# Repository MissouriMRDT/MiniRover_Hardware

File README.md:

# Mini Rover 
A board to control the drivetrain, arm, and LED panel of a miniature rover. The miniature rover can be controlled via a web interface on the user’s phone served over a wifi access point by the mini rover. 

[Main Project Document](https://mailmissouri.sharepoint.com/:w:/r/sites/SDELC-MarsRoverDesignTeam-Ogrp/_layouts/15/Doc.aspx?sourcedoc=%7B7972E1ED-EA8C-4D12-BFD3-157AE2B669ED%7D&file=Mini%20Rover.docx&action=default&mobileredirect=true)

[Discord Forum](https://discord.com/channels/988649090306961418/1412217151716196412)

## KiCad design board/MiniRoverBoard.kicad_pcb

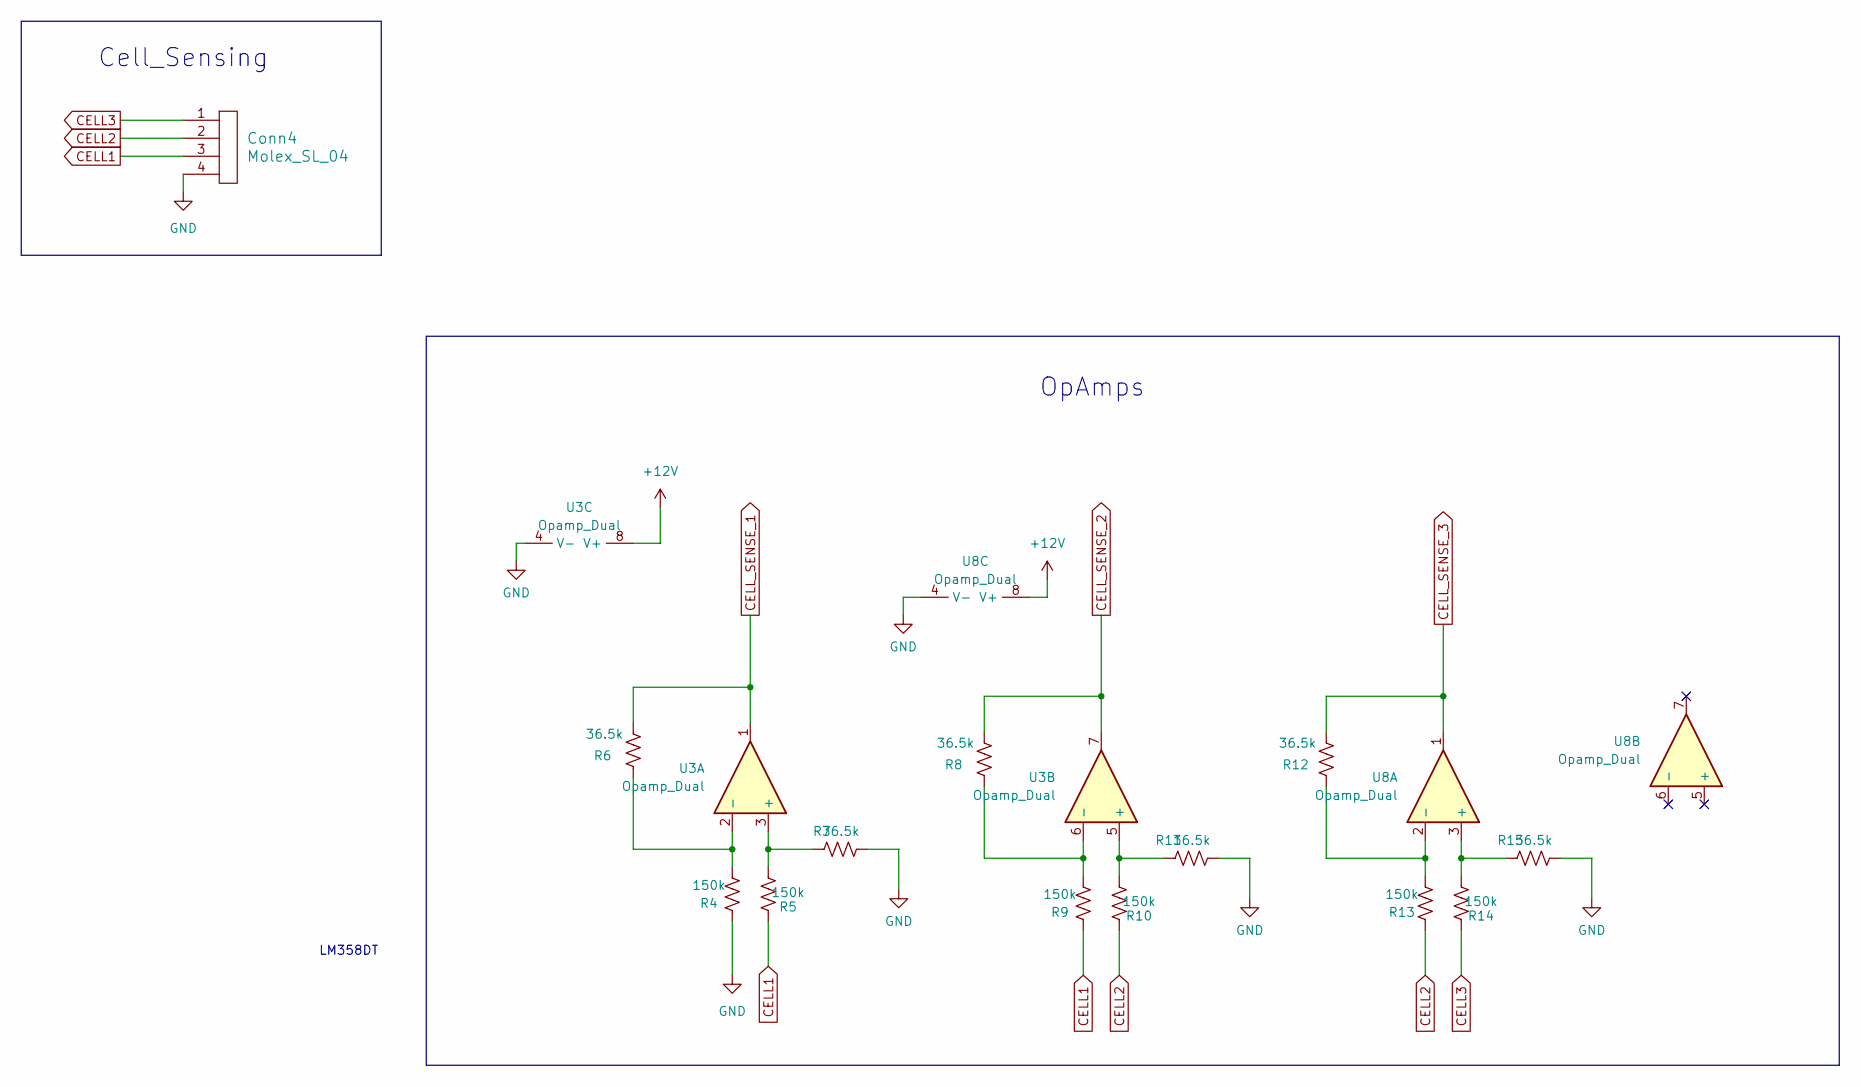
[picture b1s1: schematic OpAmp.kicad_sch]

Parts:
Conn4: Molex_SL_04; MOLEX_SL_04_Vertical
R4, R5, R9, R10, R13, R14: 150k; R_0603_1608Metric_Pad0.98x0.95mm_HandSolder
R6, R7, R8, R11, R12, R15: 36.5k; R_0603_1608Metric_Pad0.98x0.95mm_HandSolder
U3, U8: Opamp_Dual; SO-8_3.9x4.9mm_P1.27mm

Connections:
+12V: U3.8 (V+), U8.8 (V+); also elsewhere on the board
CELL1: Conn4.3, R5.1, R9.1
CELL2: Conn4.2, R10.1, R13.1
CELL3: Conn4.1, R14.1
CELL_SENSE_1: R6.2, U3.1; also elsewhere on the board
CELL_SENSE_2: R8.2, U3.7; also elsewhere on the board
CELL_SENSE_3: R12.2, U8.1; also elsewhere on the board
GND: Conn4.4, R4.1, R7.2, R11.2, R15.2, U3.4 (V-), U8.4 (V-); also elsewhere on the board
unnamed: R5.2, R7.1, U3.3 (+)
unnamed: R4.2, R6.1, U3.2 (-)
unnamed: R10.2, R11.1, U3.5 (+)
unnamed: R8.1, R9.2, U3.6 (-)
unnamed: R14.2, R15.1, U8.3 (+)
unnamed: R12.1, R13.2, U8.2 (-)

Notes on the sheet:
OpAmps
LM358DT
Cell_Sensing

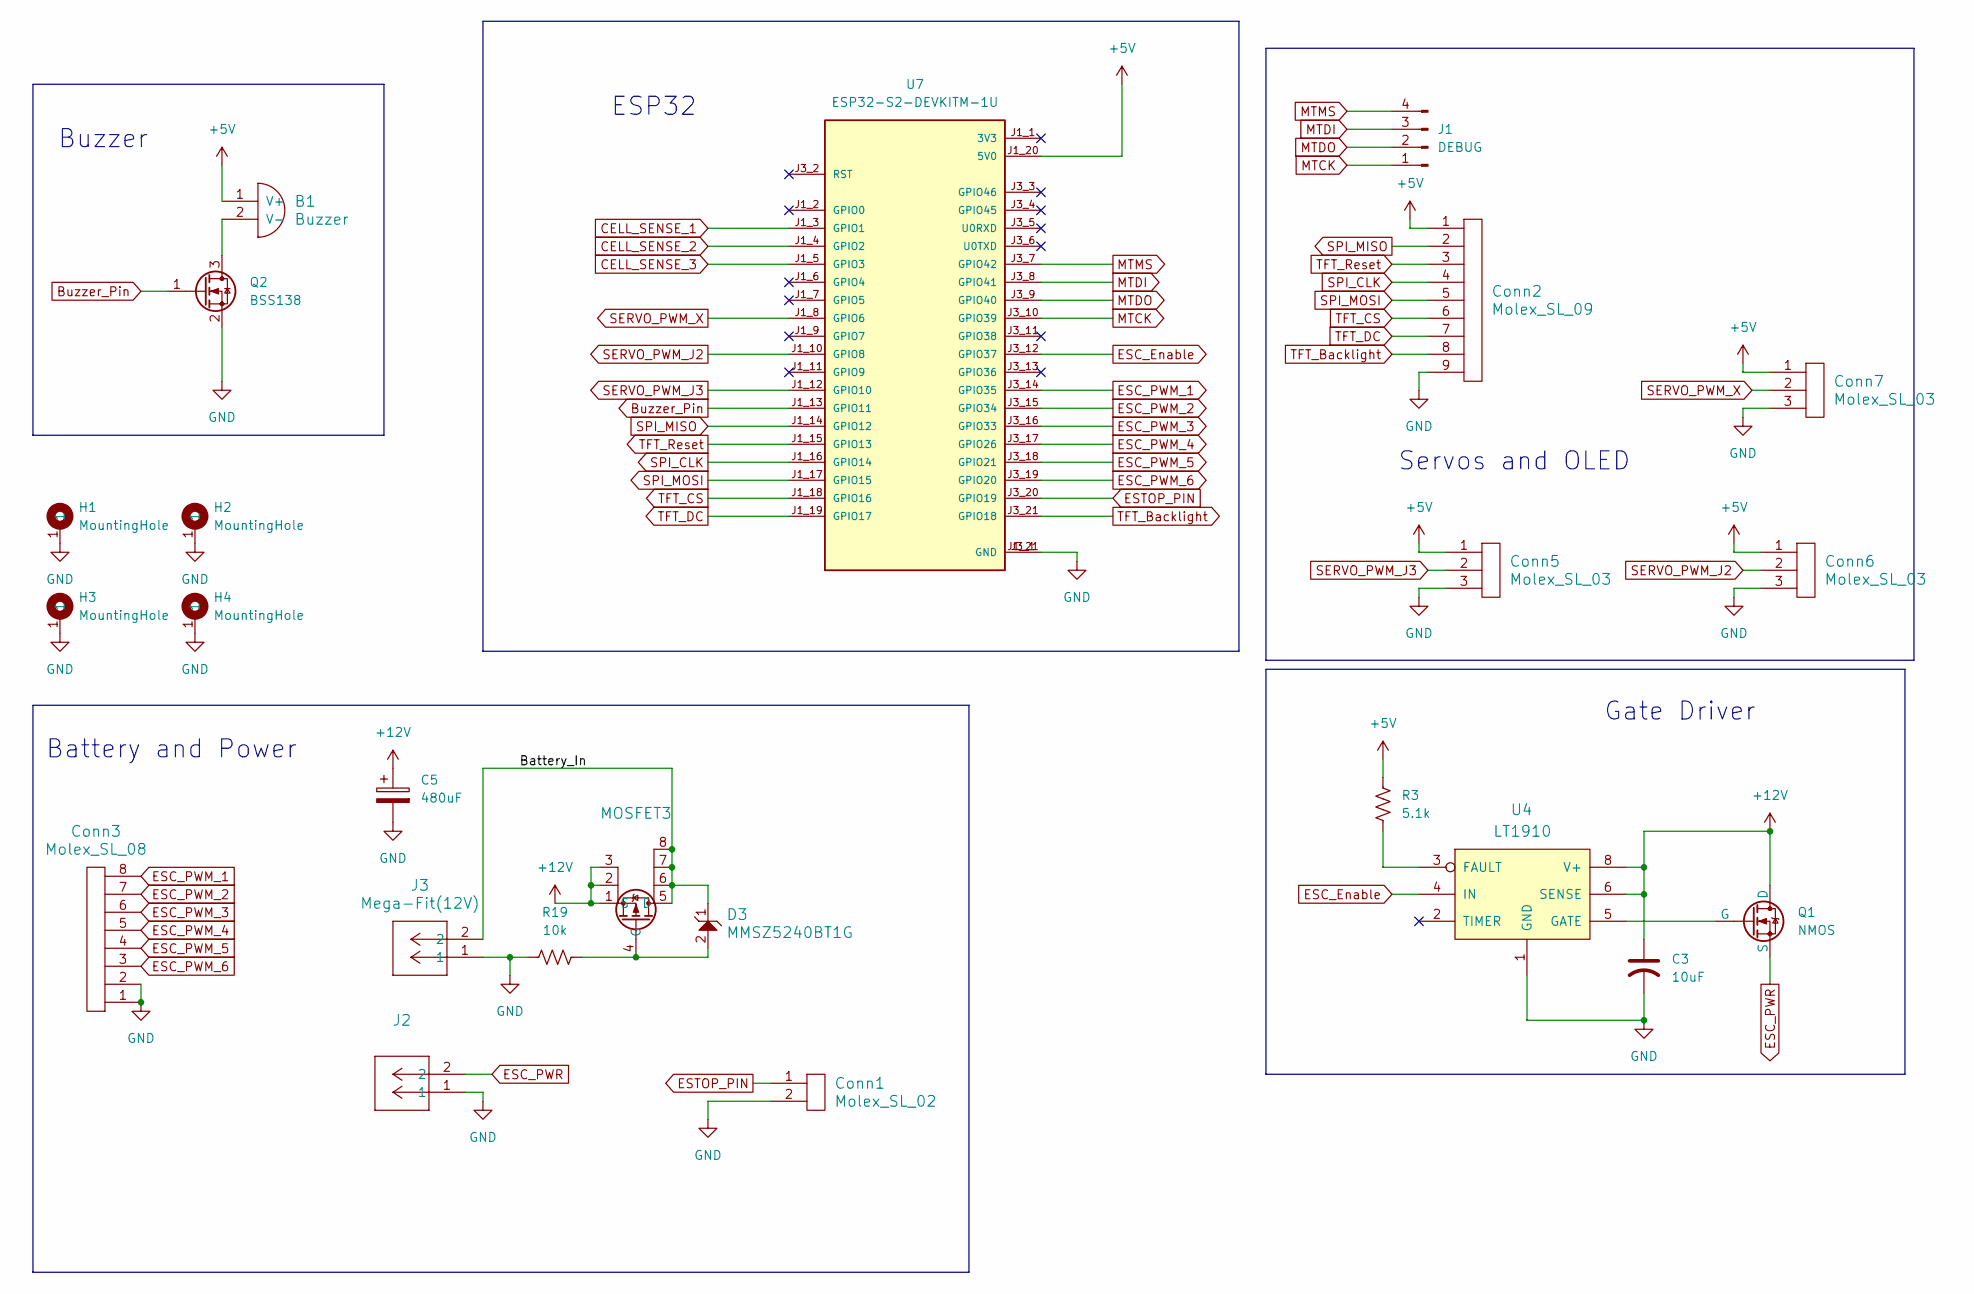
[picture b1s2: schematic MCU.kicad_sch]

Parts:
B1: Buzzer; Buzzer_12x9.5RM7.6
C3: 10uF; C_0603_1608Metric_Pad1.08x0.95mm_HandSolder
C5: 480uF; CP_Radial_D10.0mm_P5.00mm
Conn1: Molex_SL_02; MOLEX_SL_02_Vertical
Conn2: Molex_SL_09; MOLEX_SL_09_Vertical
Conn3: Molex_SL_08; MOLEX_SL_08_Vertical
Conn5, Conn6, Conn7: Molex_SL_03; MOLEX_SL_03_Vertical
D3: MMSZ5240BT1G; SOD-123_ONS-L
H1, H2, H3, H4: MountingHole; 4_40_Hole_Pad_Via
J1: DEBUG; PinSocket_1x04_P2.54mm_Vertical
J2: Mega-Fit(ESC_PWR); MOLEX_MegaFit_02_Horizontal
J3: Mega-Fit(12V); MOLEX_MegaFit_02_Horizontal
MOSFET3: TPC8132_LQS; SOP-8_TOS-L
Q1: NMOS; TO-252-3_TabPin2
Q2: BSS138; SOT-23
R3: 5.1k; R_0603_1608Metric_Pad0.98x0.95mm_HandSolder
R19: 10k; R_0603_1608Metric_Pad0.98x0.95mm_HandSolder
U4: LT1910; SOIC-8_3.9x4.9mm_P1.27mm
U7: ESP32-S2-DEVKITM-1U; XCVR_ESP32-S2-DEVKITM-1U; PARTREV 1.0

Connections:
+5V: B1.1 (V+), Conn2.1, Conn5.1, Conn6.1, Conn7.1, R3.1, U7.J1_20 (5V0); also elsewhere on the board
+12V: C3.1, C5.1, MOSFET3.1 (S), MOSFET3.2, MOSFET3.3, Q1.2 (D), U4.6 (SENSE), U4.8 (V+); also elsewhere on the board
/MCU/Battery_In: D3.1, J3.2, MOSFET3.5 (D), MOSFET3.6, MOSFET3.7, MOSFET3.8
Buzzer_Pin: Q2.1 (G), U7.J1_13 (GPIO11)
CELL_SENSE_1: U7.J1_3 (GPIO1); also elsewhere on the board
CELL_SENSE_2: U7.J1_4 (GPIO2); also elsewhere on the board
CELL_SENSE_3: U7.J1_5 (GPIO3); also elsewhere on the board
ESC_Enable: U4.4 (IN), U7.J3_12 (GPIO37)
ESC_PWM_1: Conn3.8, U7.J3_14 (GPIO35)
ESC_PWM_2: Conn3.7, U7.J3_15 (GPIO34)
ESC_PWM_3: Conn3.6, U7.J3_16 (GPIO33)
ESC_PWM_4: Conn3.5, U7.J3_17 (GPIO26)
ESC_PWM_5: Conn3.4, U7.J3_18 (GPIO21)
ESC_PWM_6: Conn3.3, U7.J3_19 (GPIO20)
ESC_PWR: J2.2, Q1.3 (S)
ESTOP_PIN: Conn1.1, U7.J3_20 (GPIO19)
GND: C3.2, C5.2, Conn1.2, Conn2.9, Conn3.1, Conn3.2, Conn5.3, Conn6.3, Conn7.3, H1.1, H2.1, H3.1, H4.1, J2.1, J3.1, Q2.2 (S), R19.1, U4.1 (GND), U7.J1_21 (GND), U7.J3_1 (GND); also elsewhere on the board
MTCK: J1.1, U7.J3_10 (GPIO39)
MTDI: J1.3, U7.J3_8 (GPIO41)
MTDO: J1.2, U7.J3_9 (GPIO40)
MTMS: J1.4, U7.J3_7 (GPIO42)
unnamed: B1.2 (V-), Q2.3 (D)
unnamed: D3.2, MOSFET3.4 (G), R19.2
unnamed: Q1.1 (G), U4.5 (GATE)
unnamed: R3.2, U4.3 (FAULT)
SERVO_PWM_J2: Conn6.2, U7.J1_10 (GPIO8)
SERVO_PWM_J3: Conn5.2, U7.J1_12 (GPIO10)
SERVO_PWM_X: Conn7.2, U7.J1_8 (GPIO6)
SPI_CLK: Conn2.4, U7.J1_16 (GPIO14)
SPI_MISO: Conn2.2, U7.J1_14 (GPIO12)
SPI_MOSI: Conn2.5, U7.J1_17 (GPIO15)
TFT_Backlight: Conn2.8, U7.J3_21 (GPIO18)
TFT_CS: Conn2.6, U7.J1_18 (GPIO16)
TFT_DC: Conn2.7, U7.J1_19 (GPIO17)
TFT_Reset: Conn2.3, U7.J1_15 (GPIO13)

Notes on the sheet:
Buzzer
Servos and OLED
Gate Driver
ESP32
Battery and Power

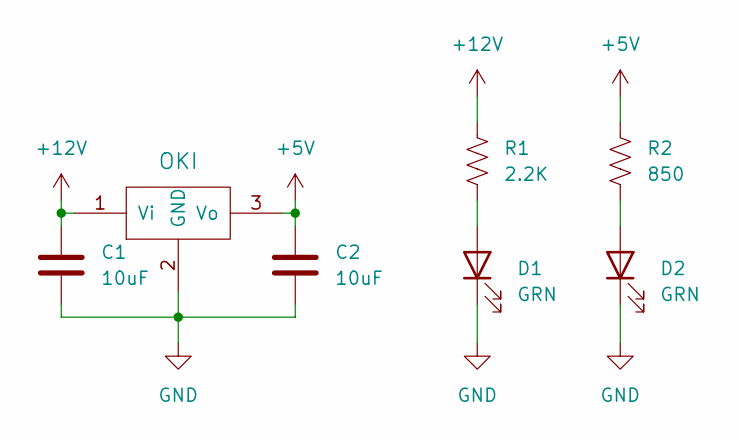
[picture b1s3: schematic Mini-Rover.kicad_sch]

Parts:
C1, C2: 10uF; C_0603_1608Metric_Pad1.08x0.95mm_HandSolder
D1, D2: GRN; LED_0603_1608Metric_Pad1.05x0.95mm_HandSolder
R1: 2.2K; R_0603_1608Metric_Pad0.98x0.95mm_HandSolder
R2: 850; R_0603_1608Metric_Pad0.98x0.95mm_HandSolder
U2: OKI; OKI_Horizontal

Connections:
+5V: C2.1, R2.1, U2.3 (Vo); also elsewhere on the board
+12V: C1.2, R1.1, U2.1 (Vi); also elsewhere on the board
GND: C1.1, C2.2, D1.1 (K), D2.1 (K), U2.2 (GND); also elsewhere on the board
unnamed: D1.2 (A), R1.2
unnamed: D2.2 (A), R2.2

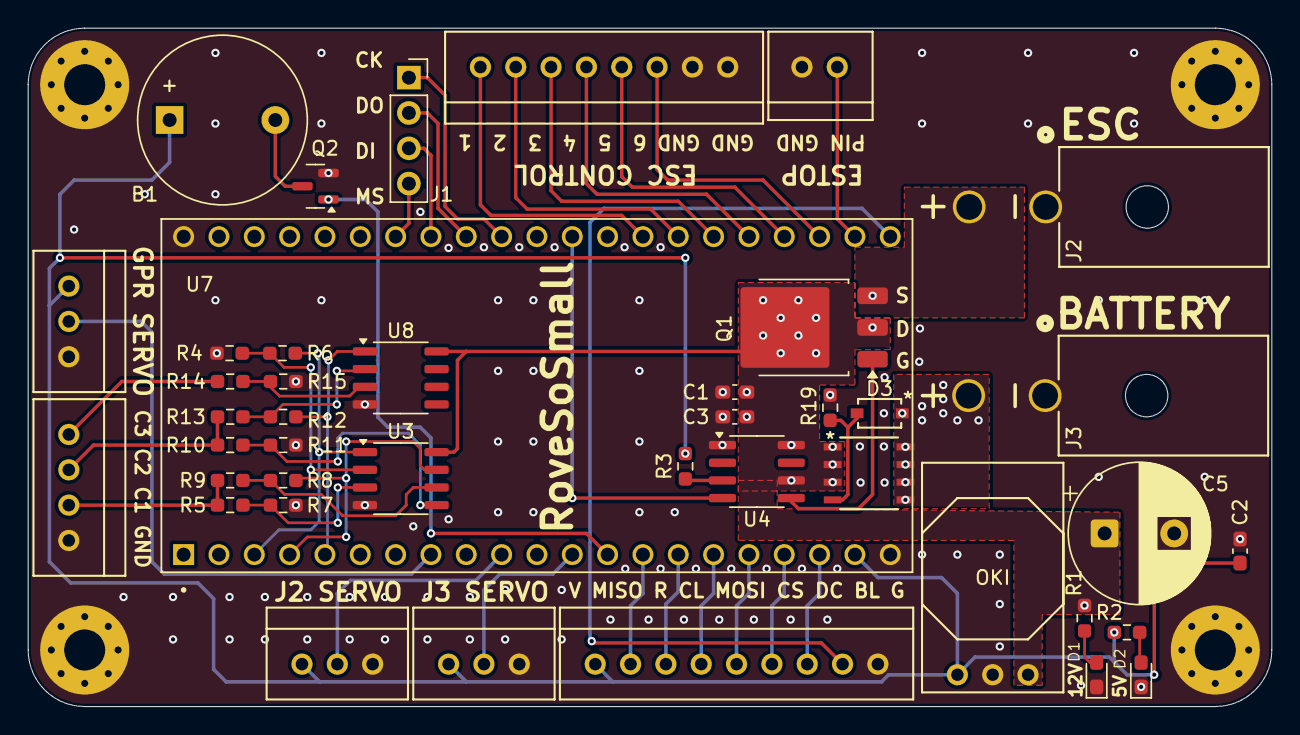
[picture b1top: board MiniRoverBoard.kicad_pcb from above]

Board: 2 copper layers, 89.4 x 48.8 mm, 46 parts (0 on the bottom side), 46 nets.

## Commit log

2025-09-12 Add workflows
2025-09-12 Added workflow
2025-10-02 Oki 12v -> 5v
2025-10-07 small fixes + 3.3V line
2025-10-07 Estop circuit
2025-10-08 Add cell sensing opamp
2025-10-08 connecting pins
2025-10-08 connections
2025-10-08 Need different mosfet/gate driver
2025-10-13 Add Gate Driver
2025-10-15 Add Gate Driver Circuit
2025-10-15 Add Gate Driver Resistor & Capacitor Values
2025-10-22 Add Gate_IN label
2025-10-23 Add OpAmp link
2025-10-23 Stop Will from sucking off Tim Cook
2025-10-24 Add Debbuger
2025-10-28 fixed some review issues and footprints
2025-10-28 Change Gate Driver and Op amp
2025-10-28 named pins + OLED pinout added
2025-10-28 fixed tags added buzzer
2025-10-29 Add Buzzer, moved PWM pins
2025-10-30 Schematic Finished
2025-10-30 Add TFT Molex Connector
2025-10-30 Add Footprint Assignments
2025-10-30 Add Layout
2025-10-30 started layout with all footprints
2025-10-31 got footprints laid out
2025-10-31 added pmos channel (still need footprints not working)
2025-11-01 Add resistor footprints for p-channel mosfets
2025-11-01 Add p-channel MOSFETs to Layout
2025-11-02 Layout started with initial dimensions
2025-11-03 Add power planes
2025-11-04 general layout placed + ground plate
2025-11-04 Add Organized OpAmp Components
2025-11-04 Add 5V trace
2025-11-05 Add 12V trace
2025-11-05 Add TFT Backlight trace
2025-11-05 Move 12 volt Oki Components next to Oki
2025-11-06 Move OpAmps and Changed buzzer footprint
2025-11-06 Add traces for OpAmps
2025-11-06 Add power traces
2025-11-07 Name everything
2025-11-10 fixed a few small issues on layout
2025-11-10 fix silkscreens
2025-11-10 Add 12 volt trace
2025-11-10 Add trace moved from under another trace
2025-11-10 Corrected 5 volt power grid
2025-11-11 Removed extra 5 volt power grid
2025-11-11 Rotate 2nd MOSFET, ADD Ground Vias, Add Names
2025-11-11 Run DRC
2025-11-11 Add net for andersons
2025-11-12 fixed font size
2025-11-12 Seperate labels
2025-11-12 Updated Dimensions
2025-11-12 Add unconnected trace on OpAmp Net
2025-11-13 Update text Thickness
2025-11-14 Vias added
2025-11-14 Readjust silkscreens and traces
2025-11-14 Add ESTOP
2025-11-14 Add Estop & ESP32 footprint
2025-11-14 Fix mounting holes, anderson net, add MRDT silkscreen
2025-11-15 Add step files
2026-01-22 Fixed Gain ratio
2026-03-11 Add Mega_Fits, Add Verticle Connectors, Add TFT GND & 5V, Changed Buzzer to pin 11, Fix Mosfet Footprint, Remove I2C
2026-03-15 Remove ESC Current Pin, Made Board smaller, Assign Mega-fit Footprints
2026-03-16 Finished layout before review
2026-03-21 Finishing touches
2026-03-23 Final board as manufactured
2026-04-01 Add Corrected Op-Amp Resistor Values
2026-04-02 Add footprint for Gate Driver Mosfet
